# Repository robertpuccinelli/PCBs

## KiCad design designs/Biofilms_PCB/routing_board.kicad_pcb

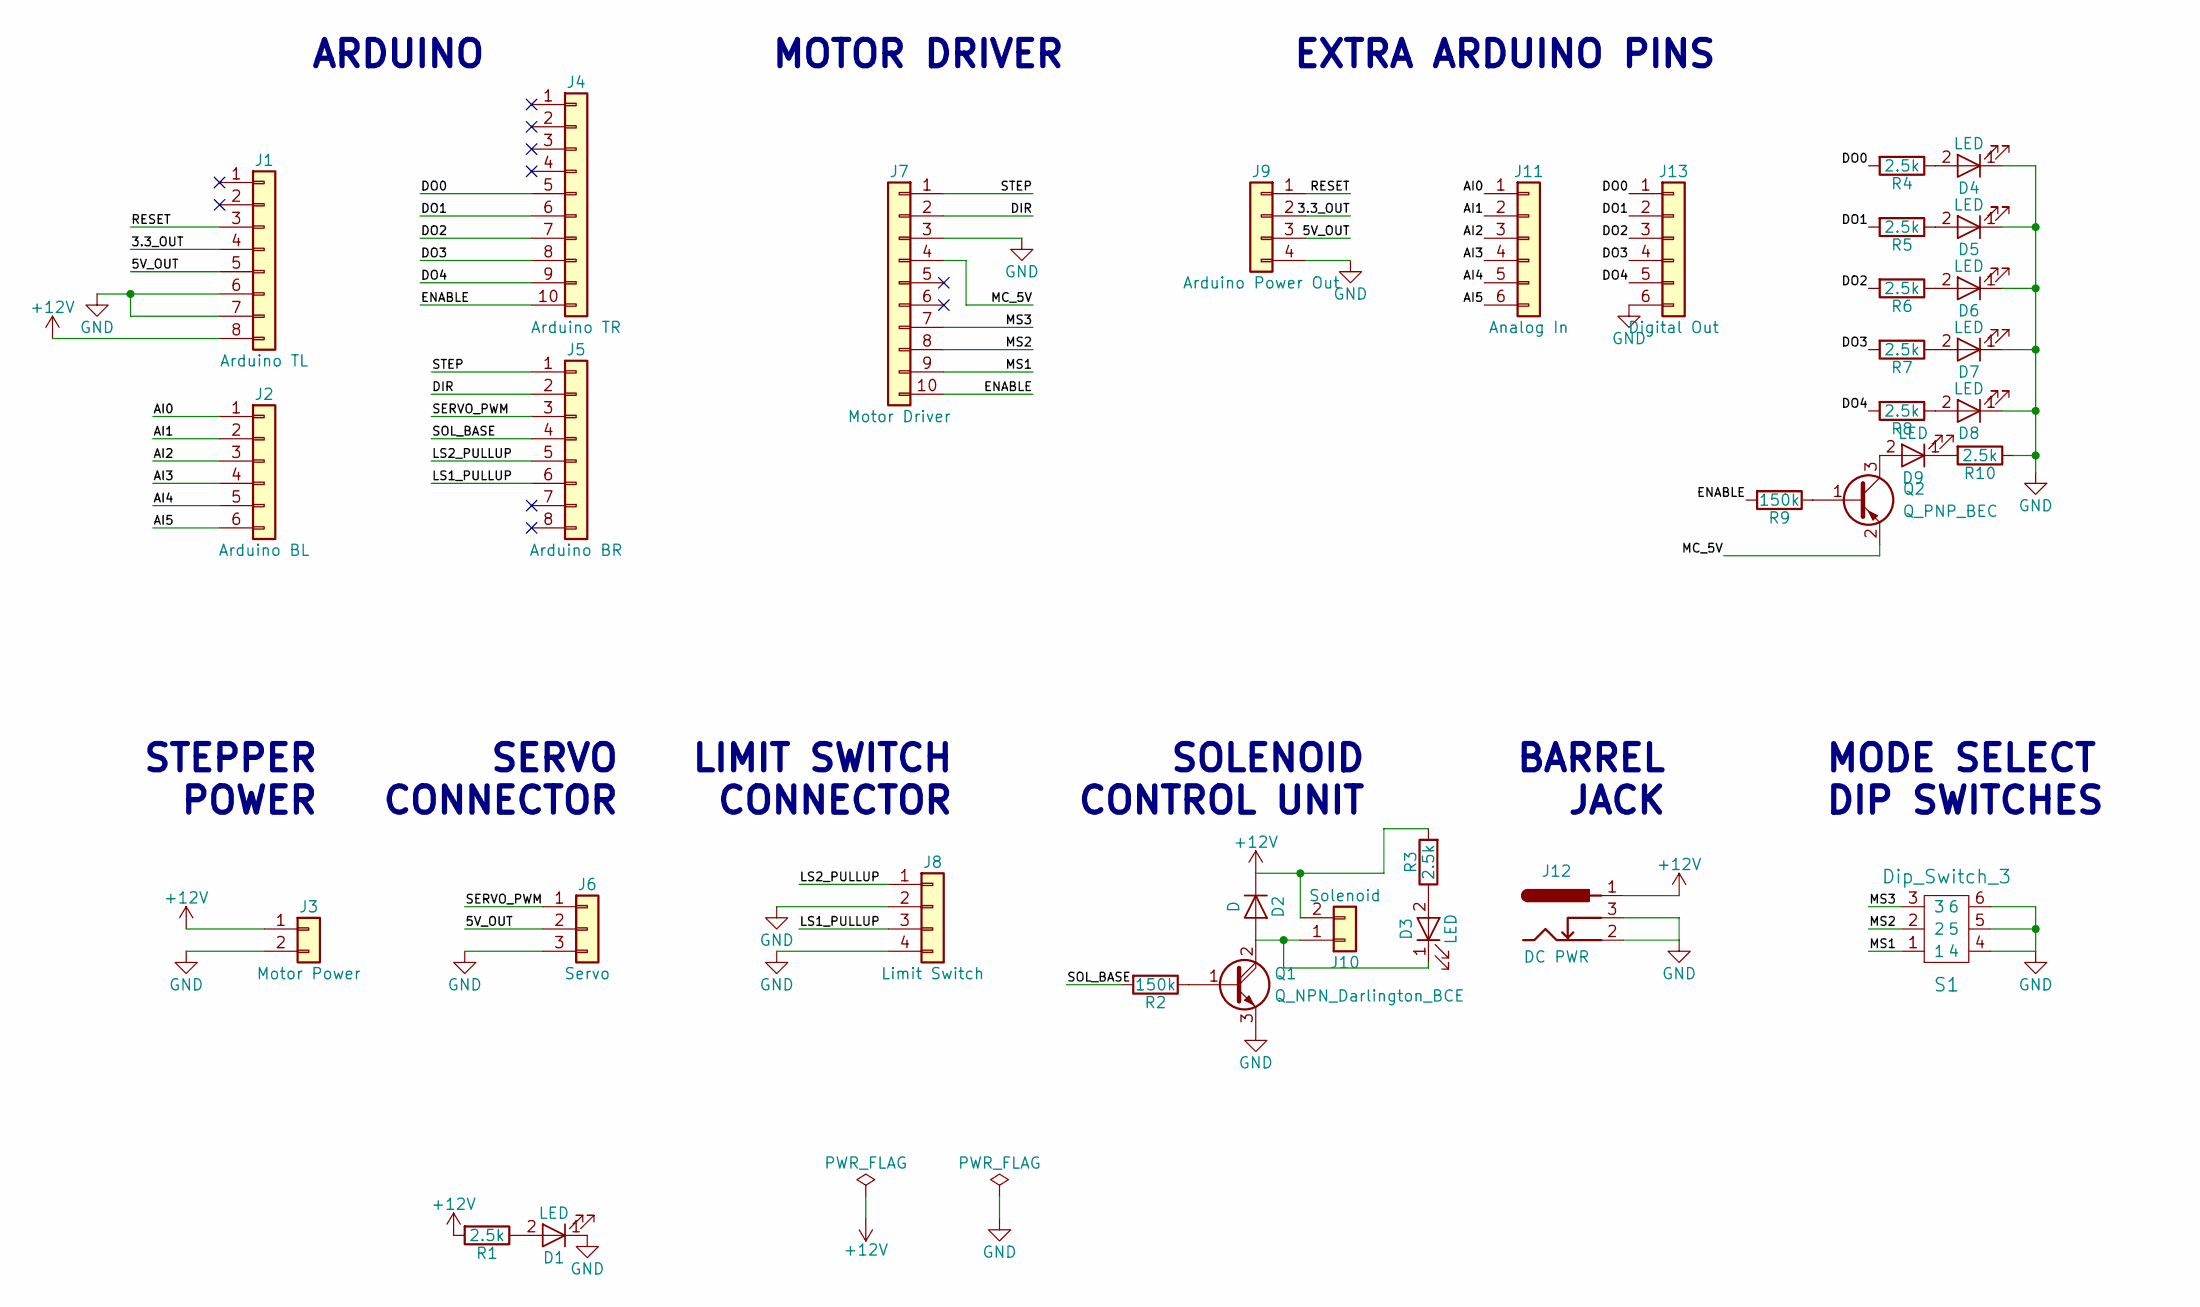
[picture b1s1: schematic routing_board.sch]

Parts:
D1, D3, D4, D5, D6, D7, D8, D9: LED; LED_0603_HandSoldering
D2: D; D_SOD-123F
J1: Arduino TL; Pin_Header_Straight_1x08_Pitch2.54mm
J2: Arduino BL; Pin_Header_Straight_1x06_Pitch2.54mm
J3: Motor Power; Socket_Strip_Straight_1x02_Pitch2.54mm
J4: Arduino TR; Pin_Header_Straight_1x10_Pitch2.54mm
J5: Arduino BR; Pin_Header_Straight_1x08_Pitch2.54mm
J6: Servo; Pin_Header_Straight_1x03_Pitch2.54mm
J7: Motor Driver; Pin_Header_Straight_1x10_Pitch2.54mm
J8: Limit Switch; Socket_Strip_Straight_1x04_Pitch2.54mm
J9: Arduino Power Out; Pin_Header_Straight_1x04_Pitch2.54mm
J10: Solenoid; Socket_Strip_Straight_1x02_Pitch2.54mm
J11: Analog In; Pin_Header_Straight_1x06_Pitch2.54mm
J12: DC PWR; BARREL_JACK
J13: Digital Out; Pin_Header_Straight_1x06_Pitch2.54mm
Q1: Q_NPN_Darlington_BCE; SOT-23
Q2: Q_PNP_BEC; SOT-23
R1, R3, R4, R5, R6, R7, R8, R10: 2.5k; R_0603_HandSoldering
R2, R9: 150k; R_0603_HandSoldering
S1: Dip_Switch_3; SW_DIP_x3_W8.61mm_Slide_LowProfile

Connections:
+12V: D2.1 (K), J1.8, J3.1, J10.2, J12.1, R1.2, R3.2
/3.3_OUT: J1.4, J9.2
/5V_OUT: J1.5, J6.2, J9.3
/AI0: J2.1, J11.1
/AI1: J2.2, J11.2
/AI2: J2.3, J11.3
/AI3: J2.4, J11.4
/AI4: J2.5, J11.5
/AI5: J2.6, J11.6
/DIR: J5.2, J7.2
/DO0: J4.5, J13.1, R4.2
/DO1: J4.6, J13.2, R5.2
/DO2: J4.7, J13.3, R6.2
/DO3: J4.8, J13.4, R7.2
/DO4: J4.9, J13.5, R8.2
/ENABLE: J4.10, J7.10, R9.2
/LS1_PULLUP: J5.6, J8.3
/LS2_PULLUP: J5.5, J8.1
/MC_5V: J7.4, Q2.2 (E)
/MS1: J7.9, S1.1
/MS2: J7.8, S1.2
/MS3: J7.7, S1.3
/RESET: J1.3, J9.1
/SERVO_PWM: J5.3, J6.1
/SOL_BASE: J5.4, R2.2
/STEP: J5.1, J7.1
GND: D1.1 (K), D4.1 (K), D5.1 (K), D6.1 (K), D7.1 (K), D8.1 (K), J1.6, J1.7, J3.2, J6.3, J7.3, J8.2, J8.4, J9.4, J12.2, J12.3, J13.6, Q1.3 (E), R10.1, S1.4, S1.5, S1.6
unnamed: D1.2 (A), R1.1
unnamed: D2.2 (A), D3.1 (K), J10.1, Q1.2 (C)
unnamed: D3.2 (A), R3.1
unnamed: D4.2 (A), R4.1
unnamed: D5.2 (A), R5.1
unnamed: D6.2 (A), R6.1
unnamed: D7.2 (A), R7.1
unnamed: D8.2 (A), R8.1
unnamed: D9.1 (K), R10.2
unnamed: D9.2 (A), Q2.3 (C)
unnamed: Q1.1 (B), R2.1
unnamed: Q2.1 (B), R9.1

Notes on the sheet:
ARDUINO
MOTOR DRIVER
EXTRA ARDUINO PINS
STEPPER POWER
SERVO CONNECTOR
LIMIT SWITCH CONNECTOR
SOLENOID CONTROL UNIT
BARREL JACK
MODE SELECT DIP SWITCHES

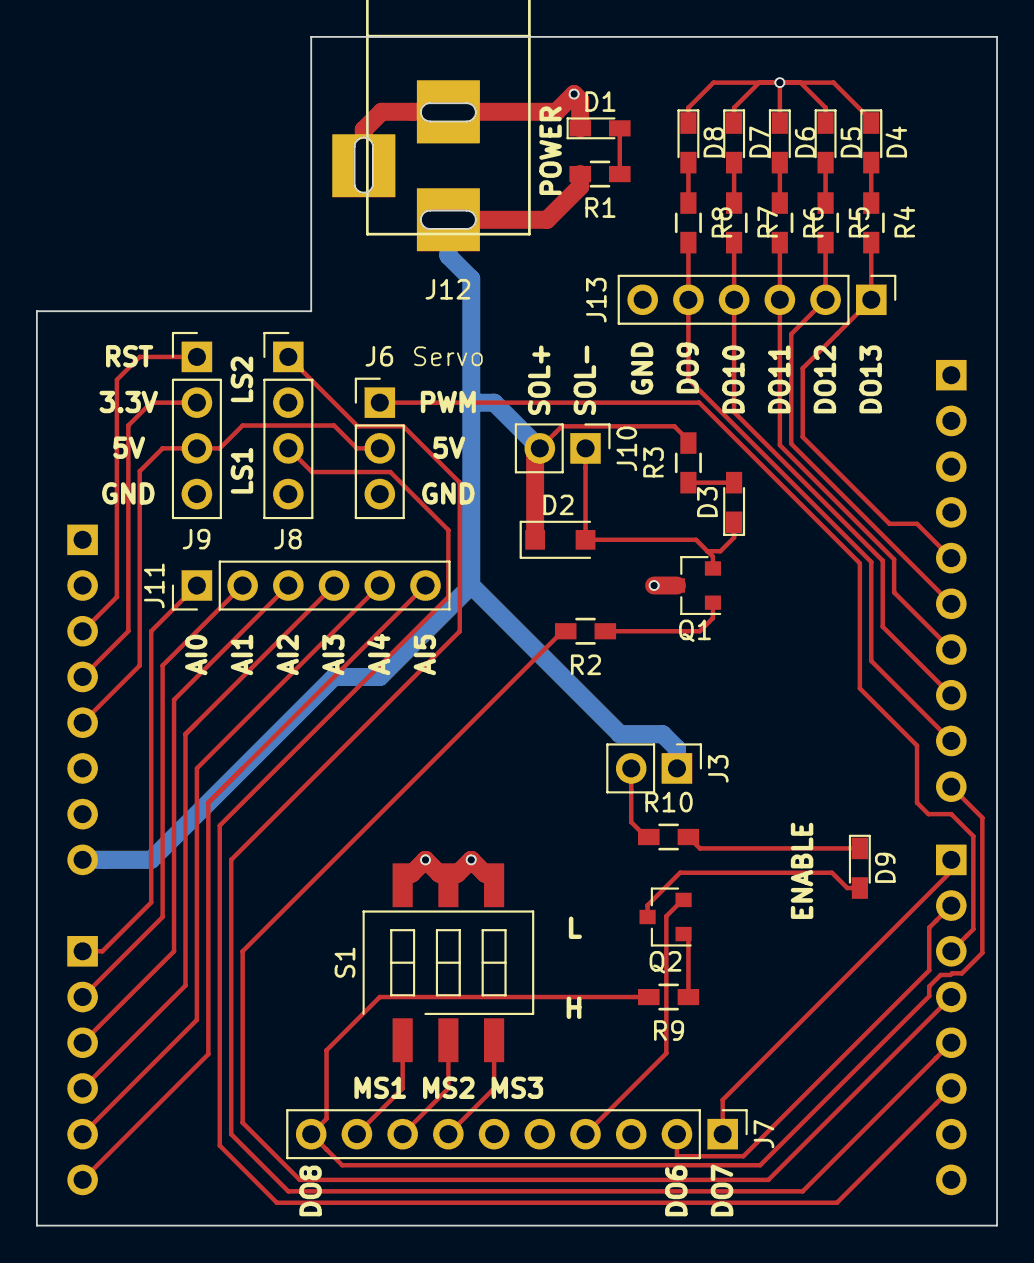
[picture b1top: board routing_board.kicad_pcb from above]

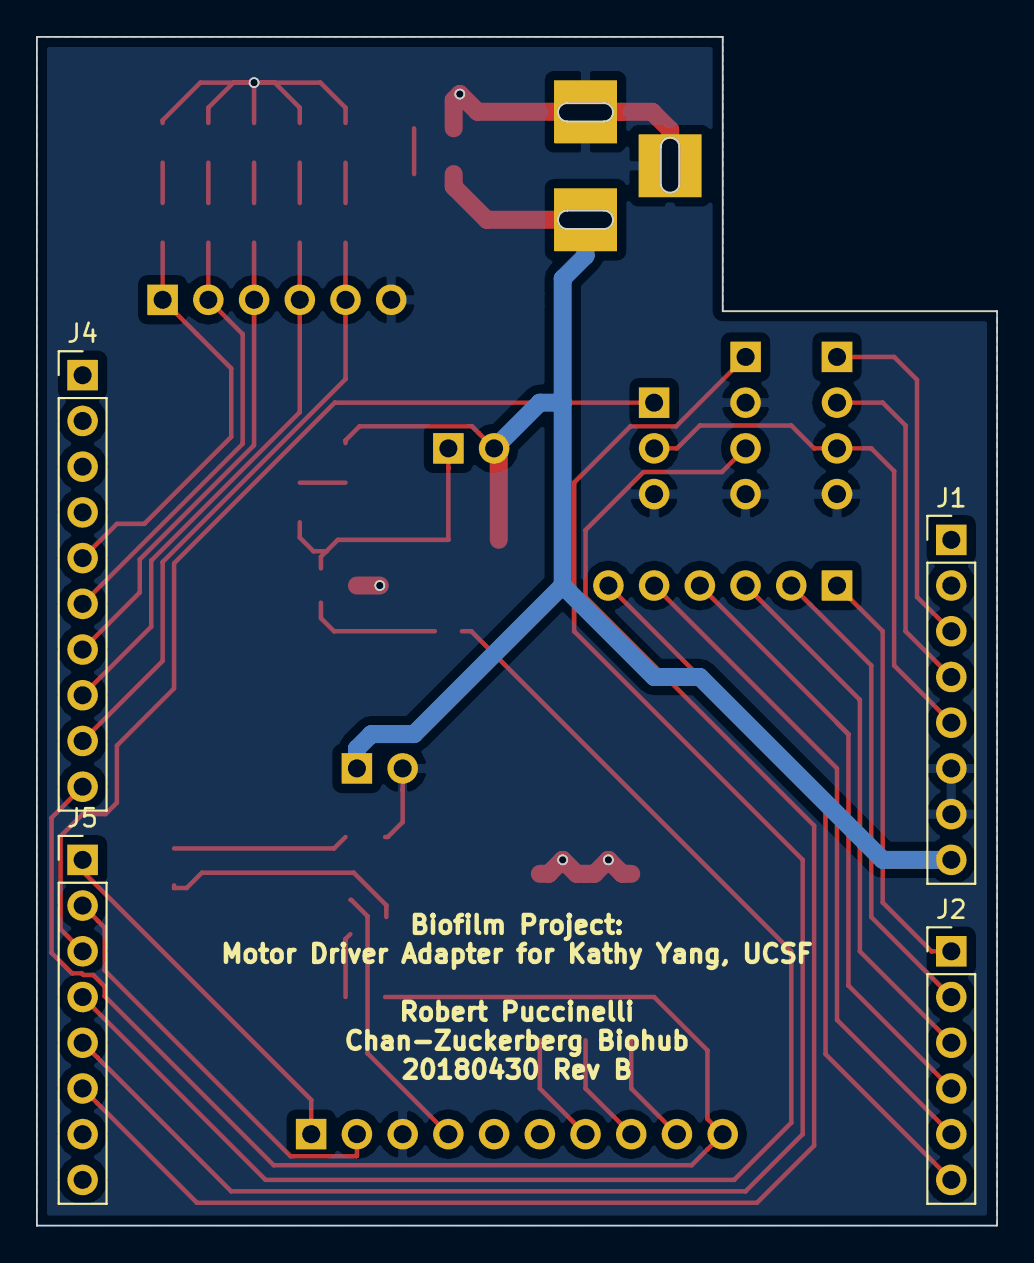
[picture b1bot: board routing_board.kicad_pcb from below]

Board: 2 copper layers, 53.3 x 66.0 mm, 35 parts (4 on the bottom side), 39 nets.

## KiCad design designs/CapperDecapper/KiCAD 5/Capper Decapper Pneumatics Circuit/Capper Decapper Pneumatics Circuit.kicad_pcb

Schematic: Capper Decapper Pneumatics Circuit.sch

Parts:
C1, C2: CP; CP_Radial_D6.3mm_P2.50mm
D1: D_Schottky; TO-220-3_Vertical
J1: 18VIn; PinHeader_1x01_P2.54mm_Vertical
J2: GNDIn; PinHeader_1x01_P2.54mm_Vertical
J3: VOut; PinHeader_1x01_P2.54mm_Vertical
J4: ENABLE; PinHeader_1x01_P2.54mm_Vertical
L1: L; L_Radial_D12.5mm_P7.00mm_Fastron_09HCP
U1: LM2574N-12; DIP-8_W7.62mm

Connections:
+VDC: C1.1, J1.1, U1.5 (VIN)
/ENABLE: J4.1, U1.3 (~ON~/OFF)
/OUT_Pin: C2.1, J3.1, L1.2, U1.1 (FB)
GND: C1.2, C2.2, D1.2, J2.1, U1.2 (SGND), U1.4 (PGND)
unnamed: D1.1, D1.3, L1.1, U1.7 (OUT)

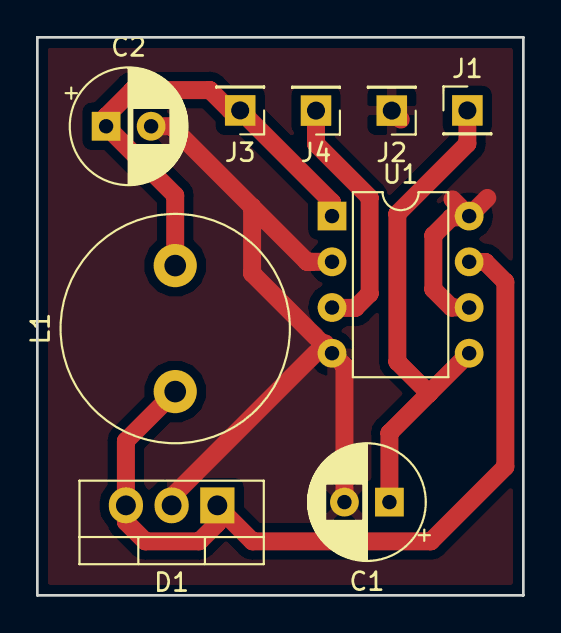
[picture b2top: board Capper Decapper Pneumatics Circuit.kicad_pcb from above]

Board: 2 copper layers, 27.0 x 31.0 mm, 9 parts (0 on the bottom side), 5 nets.

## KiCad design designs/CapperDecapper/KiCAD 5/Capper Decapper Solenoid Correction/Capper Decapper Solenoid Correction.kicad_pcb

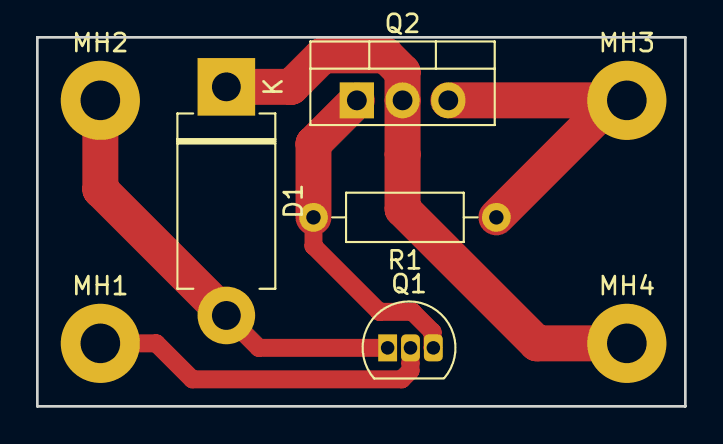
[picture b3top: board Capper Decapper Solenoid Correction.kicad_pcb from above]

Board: 2 copper layers, 36.0 x 20.5 mm, 8 parts (0 on the bottom side), 5 nets.

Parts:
D1: D; D_DO-201AD_P12.70mm_Horizontal
MH1: PI_SIGNAL; MountingHole_2.2mm_M2_Pad
MH2: GND; MountingHole_2.2mm_M2_Pad
MH3: 18V; MountingHole_2.2mm_M2_Pad
MH4: SOLENOID; MountingHole_2.2mm_M2_Pad
Q1: Q_NMOS_SGD; TO-92L_Inline
Q2: Q_PMOS_GDS; TO-220-3_Vertical
R1: R_US; R_Axial_DIN0207_L6.3mm_D2.5mm_P10.16mm_Horizontal

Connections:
unnamed: D1.1, MH4.1, Q2.2
unnamed: D1.2, MH2.1, Q1.1
unnamed: MH1.1, Q1.2
unnamed: MH3.1, Q2.3, R1.1
unnamed: Q1.3, Q2.1, R1.2

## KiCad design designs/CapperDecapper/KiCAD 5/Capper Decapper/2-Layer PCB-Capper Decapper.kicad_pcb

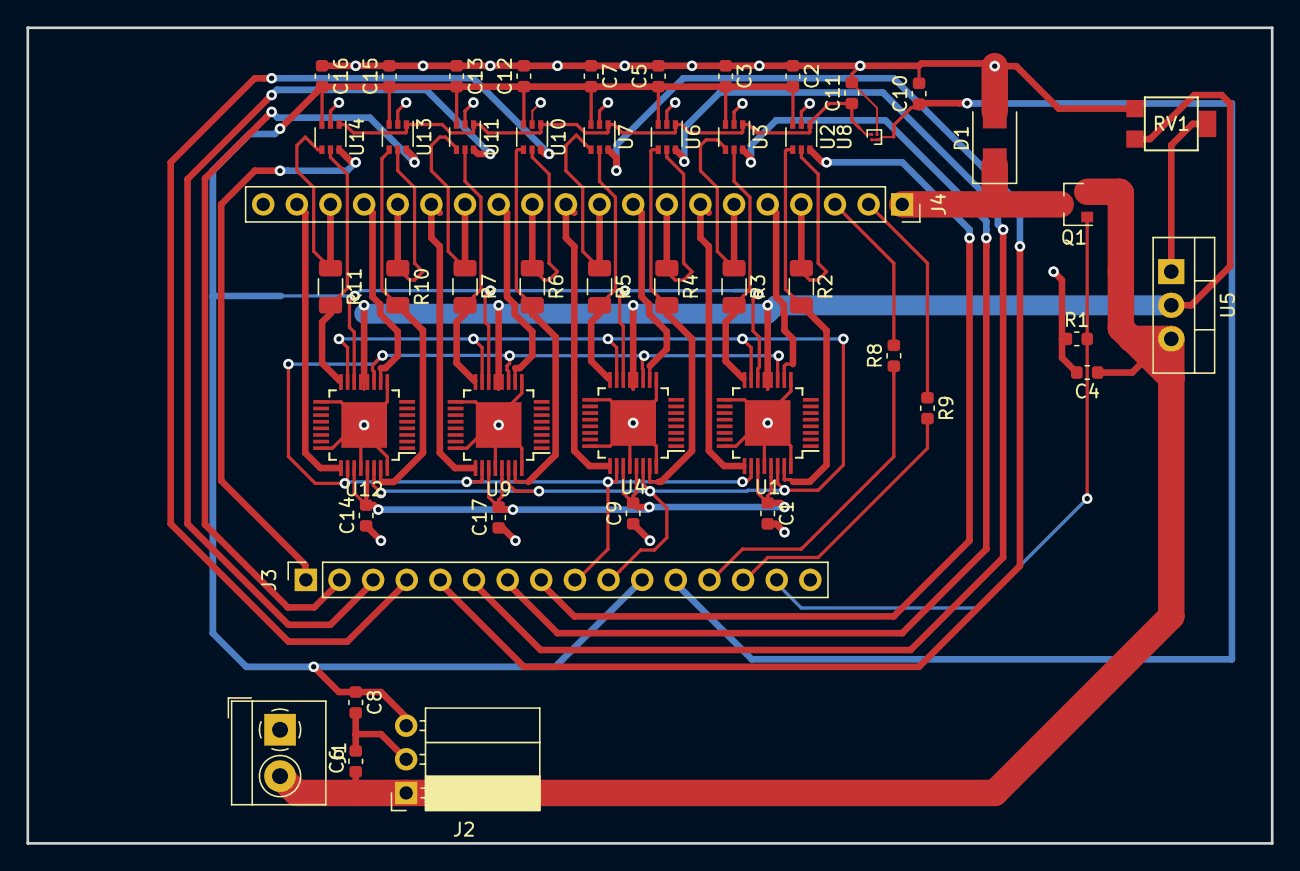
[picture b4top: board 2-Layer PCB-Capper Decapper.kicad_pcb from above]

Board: 2 copper layers, 94.0 x 61.6 mm, 49 parts (0 on the bottom side), 47 nets.

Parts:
C1, C2, C3, C4, C5, C6, C7, C8, C9, C10, C11, C12, C13, C14, C15, C16, C17: 0.01uF; C_0603_1608Metric
D1: Schottky; D_SMA
J1: Screw_Term; TerminalBlock_4Ucon_1x02_P3.50mm_Horizontal
J2: 5V_Regulator; PinSocket_1x03_P2.54mm_Horizontal
J3: Control_Signals; PinSocket_1x16_P2.54mm_Vertical
J4: Motor_Power; PinSocket_1x20_P2.54mm_Vertical
Q1: Q_NMOS_GDS; SOT-23
R1: 5k; R_0603_1608Metric
R2, R3, R4, R5, R6, R7, R10, R11: 0.05R; R_1206_3216Metric
R8, R9: 330R; R_0603_1608Metric
RV1: R_POT; R_TRIM_4mm_Gull
U1, U4, U9, U12: L2293; LQFP-32-1EP_5x5mm_P0.5mm_EP3.45x3.45mm
U2, U3, U6, U7, U10, U11, U13, U14: INA214; SOT-363_SC-70-6
U5: LM338; TO-220-3_Vertical
U8: ADP172; WLP-4_0.86x0.86mm_P0.4mm

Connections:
+36V: C4.1, C6.1, J1.2, J2.1, Q1.2, U5.3
/3.3V: C10.1, J3.12, U8.A1, U8.B1
/5V: C1.1, C2.2, C3.2, C5.1, C7.2, C8.1, C9.2, C12.1, C13.2, C14.2, C15.1, C16.2, C17.2, J2.3, J3.11, U1.14, U1.27, U1.29, U2.3, U3.3, U4.14, U4.27, U4.29, U6.3, U7.3, U9.14, U9.27, U9.29, U10.3, U11.3, U12.14, U12.27, U12.29, U13.3, U14.3
/ADC1: J3.8, U2.6
/ADC2: J3.7, U3.6
/ADC3: J3.6, U6.6
/ADC4: J3.5, U7.6
/ADC5: J3.4, U10.6
/ADC6: J3.3, U11.6
/ADC7: J3.2, U13.6
/ADC8: J3.1, U14.6
/FWD: J3.10, U1.15, U1.30, U4.15, U4.30, U9.15, U9.30, U12.15, U12.30
/MOT1_1: J4.4, R2.1, U2.5
/MOT1_2: J4.5, U1.10
/MOT2_1: J4.6, R3.1, U3.4
/MOT2_2: J4.7, U1.25
/MOT3_1: J4.8, R4.1, U6.5
/MOT3_2: J4.9, U4.10
/MOT4_1: J4.10, R5.1, U7.4
/MOT4_2: J4.11, U4.25
/MOT5_1: J4.12, R6.1, U10.5
/MOT5_2: J4.13, U9.10
/MOT6_1: J4.14, R7.1, U11.4
/MOT6_2: J4.15, U9.25
/MOT7_1: J4.16, R10.1, U13.5
/MOT7_2: J4.17, U12.10
/MOT8_1: J4.18, R11.1, U14.4
/MOT8_2: J4.19, U12.25
/REV: J3.9, U1.11, U1.26, U4.11, U4.26, U9.11, U9.26, U12.11, U12.26
/SOL+: D1.1, J4.1, Q1.3
/SOLSET: J3.15, Q1.1, R1.2
/SW1: J4.2, R9.1
/SW2: J4.3, R8.2
/V_mon: C11.1, U2.1, U3.1, U6.1, U7.1, U8.A2, U10.1, U11.1, U13.1, U14.1
/V_motor: RV1.1, U1.12, U1.13, U4.12, U4.13, U5.2, U9.12, U9.13, U12.12, U12.13
GND: C1.2, C2.1, C3.1, C4.2, C5.2, C6.2, C7.1, C8.2, C9.1, C10.2, C11.2, C12.2, C13.1, C14.1, C15.2, C16.1, C17.1, D1.2, J1.1, J2.2, J3.16, J4.20, R1.1, RV1.3, U1.9, U1.17, U1.24, U1.28, U1.32, U1.33, U2.2, U3.2, U4.9, U4.17, U4.24, U4.28, U4.32, U4.33, U6.2, U7.2, U8.B2, U9.9, U9.17, U9.24, U9.28, U9.32, U9.33, U10.2, U11.2, U12.9, U12.17, U12.24, U12.28, U12.32, U12.33, U13.2, U14.2
unnamed: J3.13, R8.1
unnamed: J3.14, R9.2
unnamed: R2.2, U1.31, U2.4
unnamed: R3.2, U1.16, U3.5
unnamed: R4.2, U4.31, U6.4
unnamed: R5.2, U4.16, U7.5
unnamed: R6.2, U9.31, U10.4
unnamed: R7.2, U9.16, U11.5
unnamed: R10.2, U12.31, U13.4
unnamed: R11.2, U12.16, U14.5
unnamed: RV1.2, U5.1

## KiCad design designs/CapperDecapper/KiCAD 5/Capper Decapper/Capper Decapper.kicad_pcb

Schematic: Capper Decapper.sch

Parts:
C1, C3, C7, C9, C13, C15, C22, C24: 22nF; C_0603_1608Metric
C2, C6, C8, C12, C14, C19, C23, C28, C29, C34, C35, C36, C37: 0.1uF; C_0603_1608Metric
C4, C10, C16, C25: 2.2uF; C_0603_1608Metric
C5, C11, C18, C27: 10nF; C_0603_1608Metric
C17, C20, C30, C31, C32, C33: 10uF; CP_EIA-3528-12_Kemet-T
C21: 0.33uF; C_0603_1608Metric
C26: 0.01uF; C_0603_1608Metric
D1, D2: Schottky; D_SMA
J1: Pi Control Signals; PinSocket_1x24_P2.54mm_Vertical
J2: Motor_Power; PinSocket_1x20_P2.54mm_Vertical
J3: Screw_Term; TerminalBlock_4Ucon_1x02_P3.50mm_Horizontal
L1: 22uH; L_Wuerth_HCI-1365
MH1, MH2: MountingHole; MountingHole_3mm
Q1: Q_NMOS_GSD; SOT-23
R1, R6, R7, R10, R12, R15, R16, R19: 0.05R; R_1206_3216Metric
R2, R5, R8, R9, R13, R14, R17, R18: 20k; R_0603_1608Metric
R3, R4: 330R; R_0603_1608Metric
R11: 5k; R_0603_1608Metric
R20: 14.2K; R_0603_1608Metric
R21: 2K; R_0603_1608Metric
U1, U4, U5, U8, U9, U12, U13, U18: INA214; SOT-363_SC-70-6
U2, U6, U10, U15: 74AHC08; PVQFN-14
U3, U7, U11, U16: DRV8833RTY; WQFN-16-1EP_4x4mm_P0.65mm_EP2.1x2.1mm
U14: L7805; TO-252-3_TabPin2
U17: MAX6018BEUR16; SOT-23
U19: AP1501A; TO-263-5_TabPin3

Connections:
/3.3V: J1.23, U17.1 (VI)
/5V: C2.1, C6.1, C8.1, C12.1, C14.1, C19.1, C23.1, C28.1, C29.2, C34.1, C35.1, C36.1, C37.1, J1.22, U1.3, U2.14, U3.15, U4.3, U5.3, U6.14, U7.15, U8.3, U9.3, U10.14, U11.15, U12.3, U13.3, U14.3, U15.14, U16.15, U18.3
/ADC1: C3.1, J1.14, R5.1
/ADC2: C1.2, J1.15, R2.2
/ADC3: C9.1, J1.16, R9.1
/ADC4: C7.2, J1.17, R8.2
/ADC5: C15.1, J1.18, R14.1
/ADC6: C13.2, J1.19, R13.2
/ADC7: C24.1, J1.20, R18.1
/ADC8: C22.2, J1.21, R17.2
/EN1: J1.4, U2.10, U2.13
/EN2: J1.5, U2.2, U2.5
/EN3: J1.6, U6.10, U6.13
/EN4: J1.7, U6.2, U6.5
/EN5: J1.8, U10.10, U10.13
/EN6: J1.9, U10.2, U10.5
/EN7: J1.10, U15.10, U15.13
/EN8: J1.11, U15.2, U15.5
/FWD: J1.13, U2.1, U2.9, U6.1, U6.9, U10.1, U10.9, U15.1, U15.9
/MOT1_1: J2.4, R6.1, U4.4
/MOT1_2: J2.5, U3.2
/MOT2_1: J2.6, R1.2, U1.5
/MOT2_2: J2.7, U3.3
/MOT3_1: J2.8, R10.1, U8.4
/MOT3_2: J2.9, U7.2
/MOT4_1: J2.10, R7.2, U5.5
/MOT4_2: J2.11, U7.3
/MOT5_1: J2.12, R15.1, U12.4
/MOT5_2: J2.13, U11.2
/MOT6_1: J2.14, R12.2, U9.5
/MOT6_2: J2.15, U11.3
/MOT7_1: J2.16, R19.1, U18.4
/MOT7_2: J2.17, U16.2
/MOT8_1: J2.18, R16.2, U13.5
/MOT8_2: J2.19, U16.3
/REV: J1.12, U2.4, U2.12, U6.4, U6.12, U10.4, U10.12, U15.4, U15.12
/SOLSET: J1.3, Q1.1, R11.2
/SW1: J2.2, R4.1
/SW2: J2.3, R3.2
/V_mon: C26.1, U1.1, U4.1, U5.1, U8.1, U9.1, U12.1, U13.1, U17.2 (VO), U18.1
/V_motor: C5.2, C11.2, C17.1, C18.2, C20.1, C27.2, C30.1, C32.1, C33.1, L1.2, R20.2, U3.10, U7.10, U11.10, U16.10
GND: C1.1, C2.2, C3.2, C4.1, C6.2, C7.1, C8.2, C9.2, C10.1, C12.2, C13.1, C14.2, C15.2, C16.1, C17.2, C19.2, C20.2, C21.1, C22.1, C23.2, C24.2, C25.1, C26.2, C28.2, C29.1, C30.2, C31.2, C32.2, C33.2, C34.2, C35.2, C36.2, C37.2, D1.2, D2.2, J1.24, J2.20, J3.1, Q1.2, R11.1, R21.2, U1.2, U2.7, U2.15, U3.1, U3.4, U3.11, U3.17, U4.2, U5.2, U6.7, U6.15, U7.1, U7.4, U7.11, U7.17, U8.2, U9.2, U10.7, U10.15, U11.1, U11.4, U11.11, U11.17, U12.2, U13.2, U14.2, U15.7, U15.15, U16.1, U16.4, U16.11, U16.17, U17.3 (GND), U18.2, U19.3, U19.5
unnamed: C4.2, U3.12
unnamed: C5.1, U3.9
unnamed: C10.2, U7.12
unnamed: C11.1, U7.9
unnamed: C16.2, U11.12
unnamed: C18.1, U11.9
unnamed: C25.2, U16.12
unnamed: C27.1, U16.9
unnamed: D2.1, L1.1, U19.2
unnamed: J1.1, R3.1
unnamed: J1.2, R4.2
unnamed: R1.1, U1.4, U3.5
unnamed: R2.1, U1.6
unnamed: R5.2, U4.6
unnamed: R6.2, U3.16, U4.5
unnamed: R7.1, U5.4, U7.5
unnamed: R8.1, U5.6
unnamed: R9.2, U8.6
unnamed: R10.2, U7.16, U8.5
unnamed: R12.1, U9.4, U11.5
unnamed: R13.1, U9.6
unnamed: R14.2, U12.6
unnamed: R15.2, U11.16, U12.5
unnamed: R16.1, U13.4, U16.5
unnamed: R17.1, U13.6
unnamed: R18.2, U18.6
unnamed: R19.2, U16.16, U18.5
unnamed: R20.1, R21.1, U19.4
unnamed: U2.3, U3.7
unnamed: U2.6, U3.8
unnamed: U2.8, U3.14
unnamed: U2.11, U3.13
unnamed: U6.3, U7.7
unnamed: U6.6, U7.8
unnamed: U6.8, U7.14
unnamed: U6.11, U7.13
unnamed: U10.3, U11.7
unnamed: U10.6, U11.8
unnamed: U10.8, U11.14
unnamed: U10.11, U11.13
unnamed: U15.3, U16.7
unnamed: U15.6, U16.8
unnamed: U15.8, U16.14
unnamed: U15.11, U16.13
VBUS: C21.2, C31.1, D1.1, J2.1, J3.2, Q1.3, U14.1, U19.1

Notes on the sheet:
Motor 9V
Solenoid Power
18V
V_monitor
Pi Control Signals
Motor Power
Half Bridges with Current Monitors

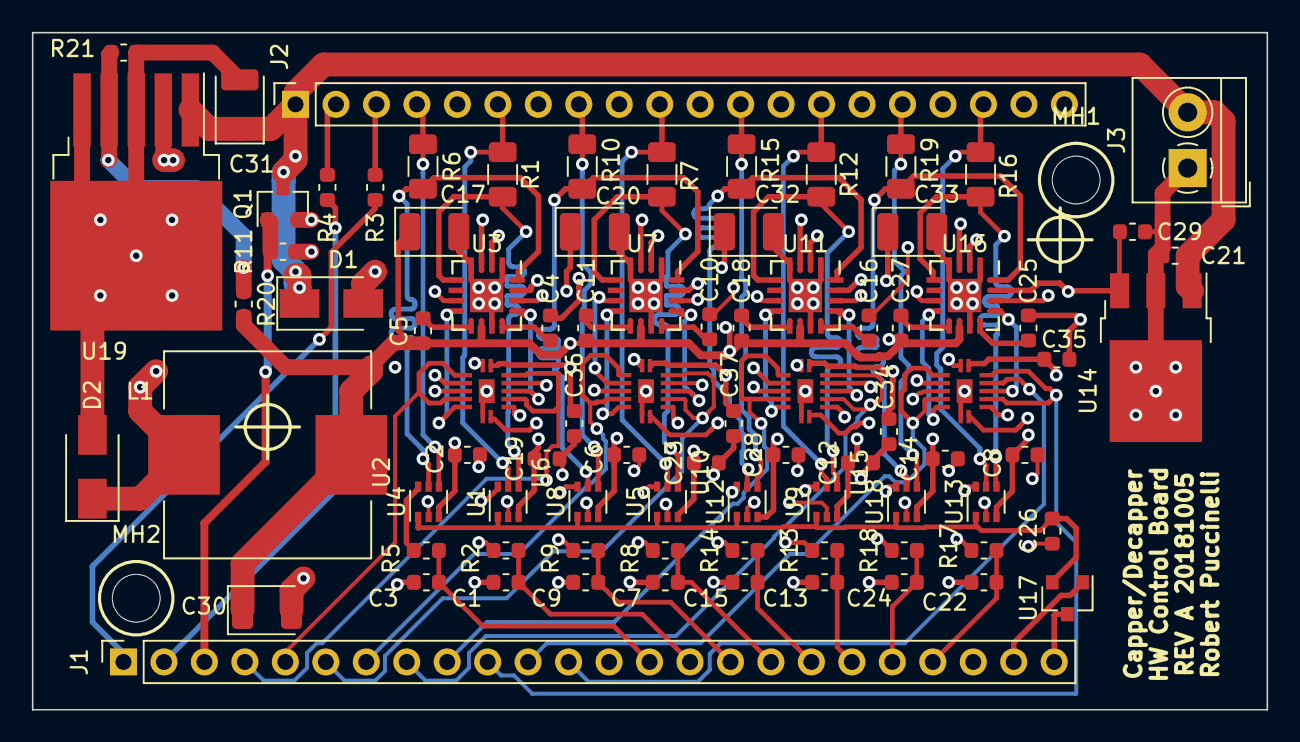
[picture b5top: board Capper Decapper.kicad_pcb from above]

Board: 4 copper layers, 77.5 x 42.5 mm, 86 parts (0 on the bottom side), 87 nets.

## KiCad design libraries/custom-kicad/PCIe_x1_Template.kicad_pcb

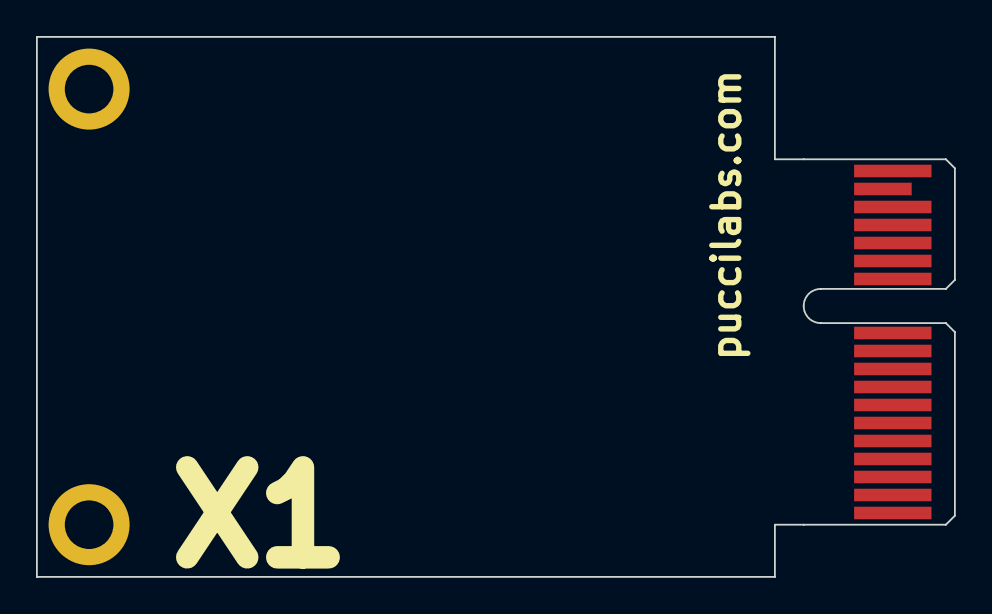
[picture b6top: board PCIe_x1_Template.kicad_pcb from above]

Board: 4 copper layers, 51.0 x 30.0 mm, 3 parts (0 on the bottom side), 4 nets, no tracks yet.

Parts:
H1, H2: MountingHole_Pad; MountingHole_2.7mm_M2.5_ISO7380_Pad
J4: PCIExpress; BUS_PCIexpress_x1

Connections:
+BATT: J4.a2, J4.a3, J4.b1, J4.b2
/TDI: J4.a6, J4.a7
GND: H1.1, H2.1, J4.a1, J4.a4, J4.a12, J4.a15, J4.a18, J4.b4, J4.b7, J4.b13, J4.b16, J4.b17, J4.b18
VBUS: J4.a9, J4.a10, J4.b8, J4.b10
